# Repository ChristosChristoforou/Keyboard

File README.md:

# Keyboard
Mechanical Keyboard PCB with four layers, two rotary encoder switches and 78 cherry-mx(pcb-mount) switches.

Parts selected are available at jlcpcb for convinience

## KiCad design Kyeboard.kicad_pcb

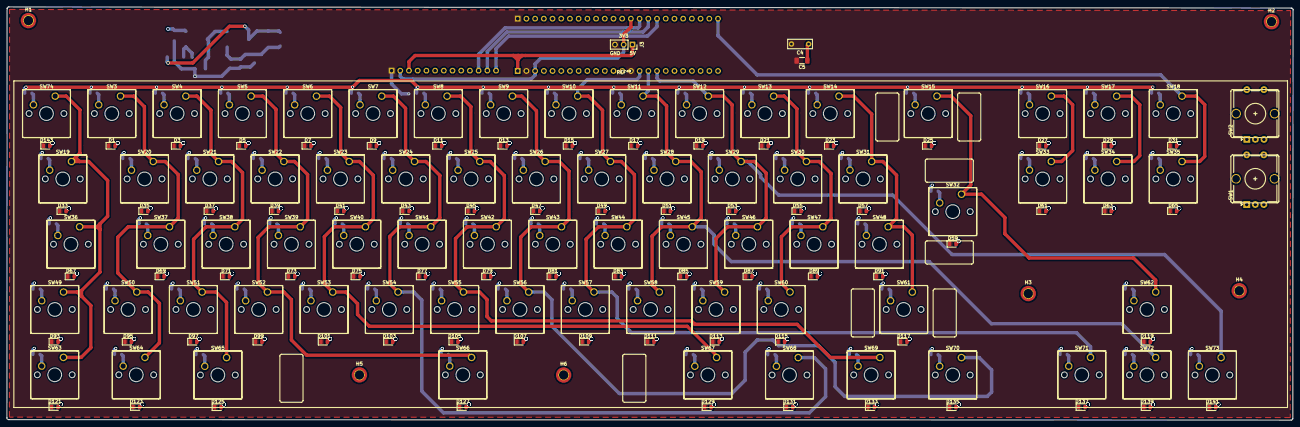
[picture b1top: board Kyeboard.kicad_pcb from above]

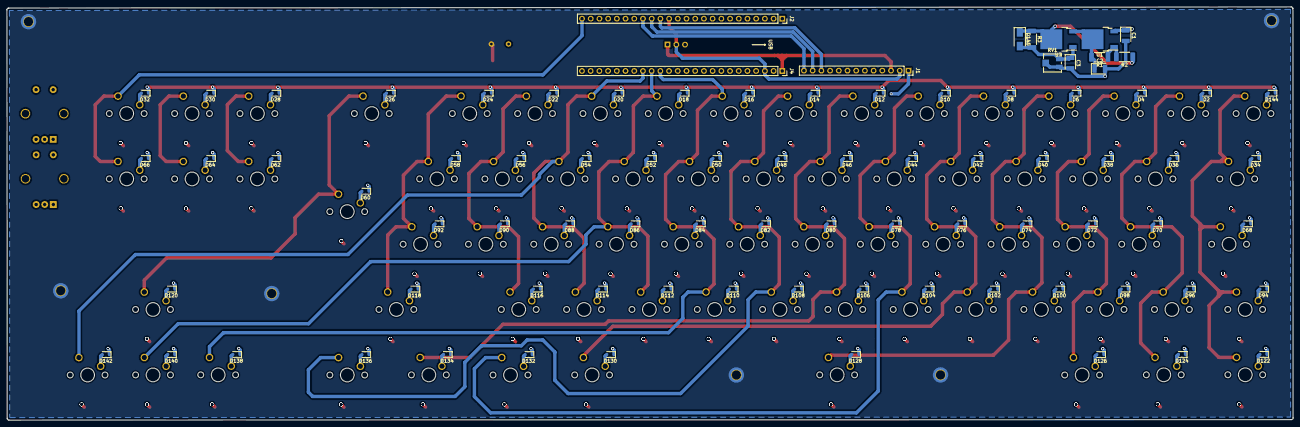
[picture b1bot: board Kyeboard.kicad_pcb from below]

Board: 4 copper layers, 375.1 x 120.5 mm, 240 parts (85 on the bottom side), 122 nets.

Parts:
C1: 0.1u/solid_tantalum; CP_EIA-3528-12_Kemet-T
C2: 1u/solid_tantalum; CP_EIA-3528-12_Kemet-T
C3: 10u/solid_tantalum; CP_EIA-3528-12_Kemet-T
C4: C; C_Disc_D7.0mm_W2.5mm_P5.00mm
C5: C; C_1206_3216Metric_Pad1.33x1.80mm_HandSolder
D1, D3, D5, D7, D9, D11, D13, D15, D17, D19, D21, D23, D25, D27, D29, D31, D33, D35, D37, D39, D41, D43, D45, D47, D49, D51, D53, D55, D57, D59, D61, D63, D65, D67, D69, D71, D73, D75, D77, D79, D81, D83, D85, D87, D89, D91, D93, D95, D97, D99, D101, D103, D105, D107, D109, D111, D113, D115, D117, D119, D121, D123, D125, D127, D129, D131, D133, D135, D137, D139, D141, D143: LED; LED_0805_2012Metric
D2, D4, D6, D8, D10, D12, D14, D16, D18, D20, D22, D24, D26, D28, D30, D32, D34, D36, D38, D40, D42, D44, D46, D48, D50, D52, D54, D56, D58, D60, D62, D64, D66, D68, D70, D72, D74, D76, D78, D80, D82, D84, D86, D88, D90, D92, D94, D96, D98, D100, D102, D104, D106, D108, D110, D112, D114, D116, D118, D120, D122, D124, D126, D128, D130, D132, D134, D136, D138, D140, D142, D144: BAT60A; D_SOD-323
D145: B120-E3; D_SMA
H1, H2, H3, H4, H5, H6: MountingHole_Pad; MountingHole_2.7mm_M2.5_ISO7380_Pad_TopBottom
J1: Conn_01x13_Male; PinSocket_1x13_P2.54mm_Vertical
J2, J4: Conn_01x24_Female; PinSocket_1x24_P2.54mm_Vertical
J3: Conn_01x03_Male; PinSocket_1x03_P2.54mm_Vertical
R1: 240; R_2010_5025Metric_Pad1.40x2.65mm_HandSolder
R2: 720; R_2010_5025Metric_Pad1.40x2.65mm_HandSolder
R3: 120; R_2010_5025Metric_Pad1.40x2.65mm_HandSolder
RV1: 1k; Potentiometer_Vishay_TS53YJ_Vertical
SW1, SW2: Rotary_Encoder_Switch; RotaryEncoder_Alps_EC12E-Switch_Vertical_H20mm_CircularMoun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
SW3, SW4, SW5, SW6, SW7, SW8, SW9, SW10, SW11, SW12, SW13, SW14, SW15, SW16, SW17, SW18, SW19, SW20, SW21, SW22, SW23, SW24, SW25, SW26, SW27, SW28, SW29, SW30, SW31, SW32, SW33, SW34, SW35, SW36, SW37, SW38, SW39, SW40, SW41, SW42, SW43, SW44, SW45, SW46, SW47, SW48, SW49, SW50, SW51, SW52, SW53, SW54, SW55, SW56, SW57, SW58, SW59, SW60, SW61, SW62, SW63, SW64, SW65, SW66, SW67, SW68, SW69, SW70, SW71, SW72, SW73, SW74: SW_Push; SW_Cherry_MX_1.00u_PCB
U1, U2: LM317_TO-252; TO-252-2

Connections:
+3V3: J1.2, J2.14, J3.2, J4.3
+5V: C1.1, J1.3, J3.1, J4.1, U1.3
/Sheet61062637/C_0: J4.7, SW19.1, SW36.1, SW49.1, SW63.1, SW74.1
/Sheet61062637/C_1: J4.6, SW3.1, SW20.1, SW37.1, SW50.1, SW64.1
/Sheet61062637/C_2: J4.5, SW4.1, SW21.1, SW38.1, SW51.1, SW65.1
/Sheet61062637/C_3: J4.4, SW5.1, SW22.1, SW39.1, SW52.1, SW66.1
/Sheet61062637/C_4: J4.12, SW6.1, SW23.1, SW40.1, SW53.1, SW67.1
/Sheet61062637/C_5: J4.11, SW7.1, SW24.1, SW41.1, SW54.1, SW68.1
/Sheet61062637/C_6: J4.10, SW8.1, SW25.1, SW42.1, SW55.1, SW69.1
/Sheet61062637/C_7: J4.9, SW9.1, SW26.1, SW43.1, SW56.1, SW70.1
/Sheet61062637/C_8: J4.15, SW10.1, SW27.1, SW44.1, SW57.1, SW71.1
/Sheet61062637/C_9: J4.16, SW11.1, SW28.1, SW45.1, SW58.1, SW72.1
/Sheet61062637/C_10: J4.17, SW12.1, SW29.1, SW46.1, SW59.1, SW73.1
/Sheet61062637/C_11: J4.18, SW13.1, SW30.1, SW47.1, SW60.1
/Sheet61062637/C_12: J4.20, SW14.1, SW31.1, SW48.1, SW61.1
/Sheet61062637/C_13: J4.23, SW15.1, SW32.1, SW62.1
/Sheet61062637/C_14: J4.22, SW16.1, SW33.1
/Sheet61062637/C_15: J4.21, SW17.1, SW34.1
/Sheet61062637/C_16: J2.24, SW18.1, SW35.1
/Sheet61062637/LED+: D1.2, D3.2, D5.2, D7.2, D9.2, D11.2, D13.2, D15.2, D17.2, D19.2, D21.2, D23.2, D25.2, D27.2, D29.2, D31.2, D33.2, D35.2, D37.2, D39.2, D41.2, D43.2, D45.2, D47.2, D49.2, D51.2, D53.2, D55.2, D57.2, D59.2, D61.2, D63.2, D65.2, D67.2, D69.2, D71.2, D73.2, D75.2, D77.2, D79.2, D81.2, D83.2, D85.2, D87.2, D89.2, D91.2, D93.2, D95.2, D97.2, D99.2, D101.2, D103.2, D105.2, D107.2, D109.2, D111.2, D113.2, D115.2, D117.2, D119.2, D121.2, D123.2, D125.2, D127.2, D129.2, D131.2, D133.2, D135.2, D137.2, D139.2, D141.2, D143.2, D145.1, R2.1, R3.1, U2.2
/Sheet61062637/R_0: D2.1, D4.1, D6.1, D8.1, D10.1, D12.1, D14.1, D16.1, D18.1, D20.1, D22.1, D24.1, D26.1, D28.1, D30.1, D32.1, D144.1, J4.8
/Sheet61062637/R_1: D34.1, D36.1, D38.1, D40.1, D42.1, D44.1, D46.1, D48.1, D50.1, D52.1, D54.1, D56.1, D58.1, D60.1, D62.1, D64.1, D66.1, J4.13
/Sheet61062637/R_2: D68.1, D70.1, D72.1, D74.1, D76.1, D78.1, D80.1, D82.1, D84.1, D86.1, D88.1, D90.1, D92.1, J4.19
/Sheet61062637/R_3: D94.1, D96.1, D98.1, D100.1, D102.1, D104.1, D106.1, D108.1, D110.1, D112.1, D114.1, D116.1, D118.1, D120.1, J4.24
/Sheet61062637/R_4: D122.1, D124.1, D126.1, D128.1, D130.1, D132.1, D134.1, D136.1, D138.1, D140.1, D142.1, J2.23
GNDREF: C1.2, C2.2, C3.2, C4.2, C5.2, D1.1, D3.1, D5.1, D7.1, D9.1, D11.1, D13.1, D15.1, D17.1, D19.1, D21.1, D23.1, D25.1, D27.1, D29.1, D31.1, D33.1, D35.1, D37.1, D39.1, D41.1, D43.1, D45.1, D47.1, D49.1, D51.1, D53.1, D55.1, D57.1, D59.1, D61.1, D63.1, D65.1, D67.1, D69.1, D71.1, D73.1, D75.1, D77.1, D79.1, D81.1, D83.1, D85.1, D87.1, D89.1, D91.1, D93.1, D95.1, D97.1, D99.1, D101.1, D103.1, D105.1, D107.1, D109.1, D111.1, D113.1, D115.1, D117.1, D119.1, D121.1, D123.1, D125.1, D127.1, D129.1, D131.1, D133.1, D135.1, D137.1, D139.1, D141.1, D143.1, J1.1, J2.1, J3.3, J4.2, J4.14, RV1.2, RV1.3
unnamed: C2.1, R1.2, U1.2, U2.3
unnamed: C3.1, D145.2, R3.2, RV1.1, U2.1
unnamed: C4.1, C5.1, H1.1, H2.1, H3.1, H4.1, H5.1, H6.1
unnamed: D2.2, SW3.2
unnamed: D4.2, SW4.2
unnamed: D6.2, SW5.2
unnamed: D8.2, SW6.2
unnamed: D10.2, SW7.2
unnamed: D12.2, SW8.2
unnamed: D14.2, SW9.2
unnamed: D16.2, SW10.2
unnamed: D18.2, SW11.2
unnamed: D20.2, SW12.2
unnamed: D22.2, SW13.2
unnamed: D24.2, SW14.2
unnamed: D26.2, SW15.2
unnamed: D28.2, SW16.2
unnamed: D30.2, SW17.2
unnamed: D32.2, SW18.2
unnamed: D34.2, SW19.2
unnamed: D36.2, SW20.2
unnamed: D38.2, SW21.2
unnamed: D40.2, SW22.2
unnamed: D42.2, SW23.2
unnamed: D44.2, SW24.2
unnamed: D46.2, SW25.2
unnamed: D48.2, SW26.2
unnamed: D50.2, SW27.2
unnamed: D52.2, SW28.2
unnamed: D54.2, SW29.2
unnamed: D56.2, SW30.2
unnamed: D58.2, SW31.2
unnamed: D60.2, SW32.2
unnamed: D62.2, SW33.2
unnamed: D64.2, SW34.2
unnamed: D66.2, SW35.2
unnamed: D68.2, SW36.2
unnamed: D70.2, SW37.2
unnamed: D72.2, SW38.2
unnamed: D74.2, SW39.2
unnamed: D76.2, SW40.2
unnamed: D78.2, SW41.2
unnamed: D80.2, SW42.2
unnamed: D82.2, SW43.2
unnamed: D84.2, SW44.2
unnamed: D86.2, SW45.2
unnamed: D88.2, SW46.2
unnamed: D90.2, SW47.2
unnamed: D92.2, SW48.2
unnamed: D94.2, SW49.2
unnamed: D96.2, SW50.2
unnamed: D98.2, SW51.2
unnamed: D100.2, SW52.2
unnamed: D102.2, SW53.2
unnamed: D104.2, SW54.2
unnamed: D106.2, SW55.2
unnamed: D108.2, SW56.2
unnamed: D110.2, SW57.2
unnamed: D112.2, SW58.2
unnamed: D114.2, SW59.2
unnamed: D116.2, SW60.2
unnamed: D118.2, SW61.2
unnamed: D120.2, SW62.2
unnamed: D122.2, SW63.2
unnamed: D124.2, SW64.2
unnamed: D126.2, SW65.2
unnamed: D128.2, SW66.2
unnamed: D130.2, SW67.2
unnamed: D132.2, SW68.2
unnamed: D134.2, SW69.2
unnamed: D136.2, SW70.2
unnamed: D138.2, SW71.2
unnamed: D140.2, SW72.2
unnamed: D142.2, SW73.2
unnamed: D144.2, SW74.2
unnamed: J1.4, J2.2
unnamed: J1.5, J2.3
unnamed: J1.6, J2.4
unnamed: J1.7, J2.5
unnamed: J1.8, J2.6
unnamed: J1.9, J2.7
unnamed: J1.10, J2.8
unnamed: J1.11, J2.15
unnamed: J1.12, J2.16
unnamed: J1.13, J2.17
unnamed: J2.9, SW1.B
unnamed: J2.10, SW1.C
unnamed: J2.11, SW1.A
unnamed: J2.12, SW1.S1
unnamed: J2.13, SW1.S2
unnamed: J2.18, SW2.B
unnamed: J2.19, SW2.C
unnamed: J2.20, SW2.A
unnamed: J2.21, SW2.S1
unnamed: J2.22, SW2.S2
unnamed: R1.1, R2.2, U1.1
